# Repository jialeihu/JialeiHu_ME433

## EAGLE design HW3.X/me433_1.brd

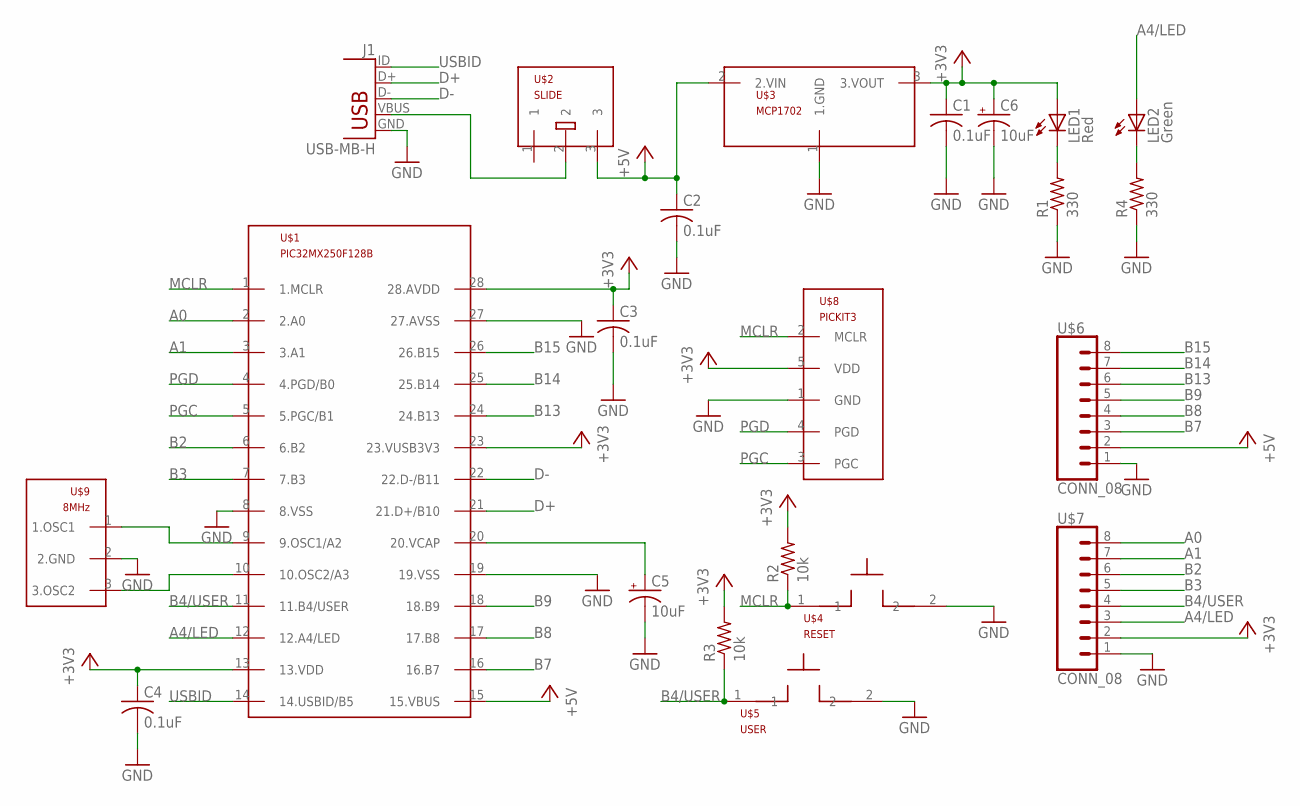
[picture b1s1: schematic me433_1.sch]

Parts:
C1, C2, C3, C4: 0.1uF; C025-025X050
C5, C6: 10uF; B45181B
J1: USB-MB-H
LED1: Red; LED3MM
LED2: Green; LED3MM
R1, R4: 330; 0207/10
R2, R3: 10k; 0207/10
U$1: PIC32MX250F128B; DIL28-3
U$2: SLIDE
U$3: MCP1702; TO92
U$4: RESET; PB
U$5: USER; PB
U$6, U$7: CONN_08; 1X08
U$8: PICKIT3; 1X05
U$9: 8MHz; OSC

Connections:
+3V3: C1.1, C3.1, C4.1, C6.+, LED1.A, R2.2, R3.2, U$1.13 (13.VDD), U$1.23 (23.VUSB3V3), U$1.28 (28.AVDD), U$3.3 (3.VOUT), U$7.2, U$8.5 (VDD)
+5V: C2.1, U$1.15 (15.VBUS), U$2.3, U$3.2 (2.VIN), U$6.2
A0: U$1.2 (2.A0), U$7.8
A1: U$1.3 (3.A1), U$7.7
A4/LED: LED2.A, U$1.12 (12.A4/LED), U$7.3
B2: U$1.6 (6.B2), U$7.6
B3: U$1.7 (7.B3), U$7.5
B4/USER: R3.1, U$1.11 (11.B4/USER), U$5.1, U$7.4
B7: U$1.16 (16.B7), U$6.3
B8: U$1.17 (17.B8), U$6.4
B9: U$1.18 (18.B9), U$6.5
B13: U$1.24 (24.B13), U$6.6
B14: U$1.25 (25.B14), U$6.7
B15: U$1.26 (26.B15), U$6.8
D+: J1.D+, U$1.21 (21.D+/B10)
D-: J1.D-, U$1.22 (22.D-/B11)
GND: C1.2, C2.2, C3.2, C4.2, C5.-, C6.-, J1.GND, R1.1, R4.1, U$1.8 (8.VSS), U$1.19 (19.VSS), U$1.27 (27.AVSS), U$3.1 (1.GND), U$4.2, U$5.2, U$6.1, U$7.1, U$8.1 (GND), U$9.2 (2.GND)
MCLR: R2.1, U$1.1 (1.MCLR), U$4.1, U$8.2 (MCLR)
unnamed: J1.VBUS, U$2.2
unnamed: LED2.K (C), R4.2
unnamed: LED1.K (C), R1.2
unnamed: U$1.9 (9.OSC1/A2), U$9.1 (1.OSC1)
unnamed: U$1.10 (10.OSC2/A3), U$9.3 (3.OSC2)
unnamed: C5.+, U$1.20 (20.VCAP)
PGC: U$1.5 (5.PGC/B1), U$8.3 (PGC)
PGD: U$1.4 (4.PGD/B0), U$8.4 (PGD)
USBID: J1.ID, U$1.14 (14.USBID/B5)

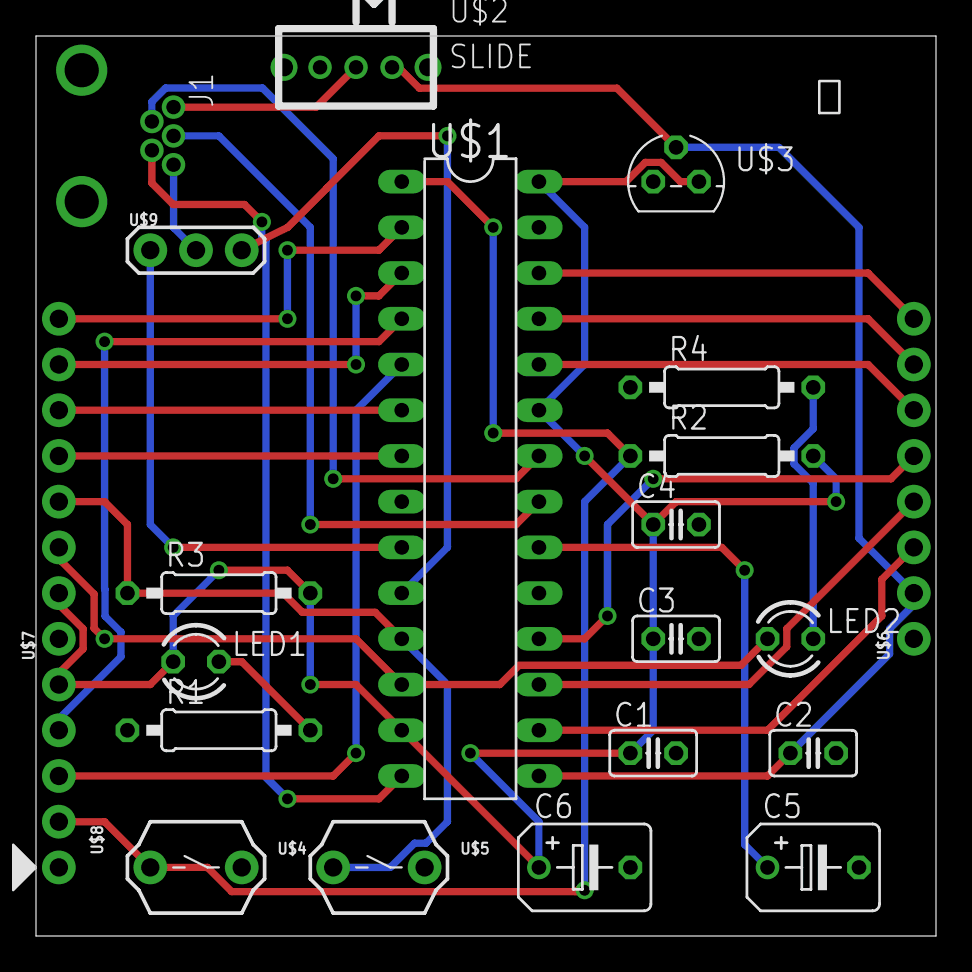
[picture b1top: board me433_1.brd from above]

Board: 2 copper layers, 50.0 x 50.0 mm, 22 parts (0 on the bottom side), 27 nets.

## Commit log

2017-03-29 :tada: Added .gitattributes & .gitignore files
2017-03-29 main
2017-05-08 HW12
2017-05-14 HW10
2017-05-14 HW11
2017-05-16 HW13
2017-05-25 HW14
2017-05-25 HW15
2017-05-25 HW16
2017-05-25 HW17
2017-06-04 HW18
2017-06-07 HW19
2017-06-08 HW20
